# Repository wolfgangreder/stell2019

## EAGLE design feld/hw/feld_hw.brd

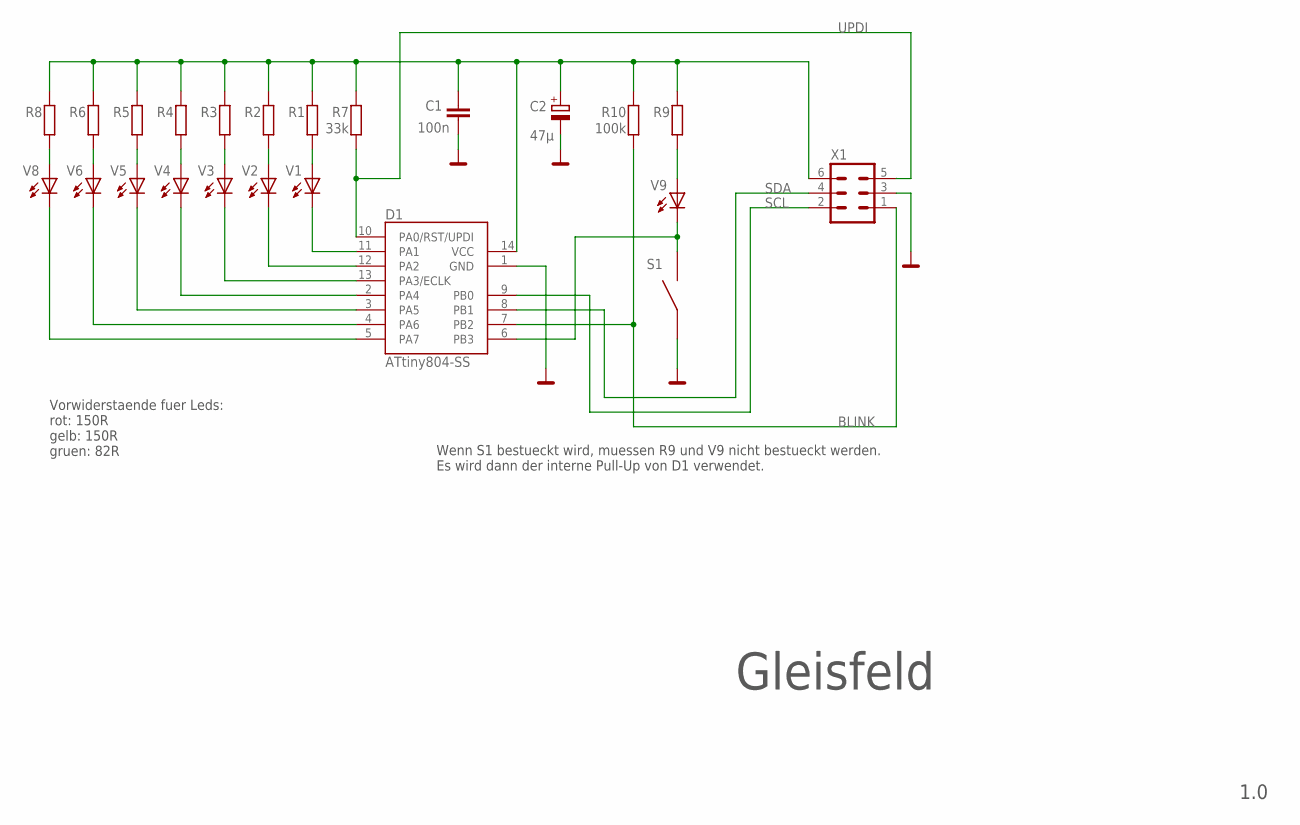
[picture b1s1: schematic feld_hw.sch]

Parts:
C1: 100n; C0805
C2: 47µ; CT7343
D1: ATtiny804-SS; SOIC14
R1, R2, R3, R4, R5, R6, R8, R9: R-EU_R0805; R0805
R7: 33k; R0805
R10: 100k; R0805
S1: 800SP9B5M2QEH; ST811004
V1, V2, V3, V4, V5, V6, V8, V9: LEDPAD; LED3MMPAD
X1: PINH2X3N; MA03/2

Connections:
BLINK: D1.7 (PB2), R10.1, X1.1
GND: C1.1, C2.-, D1.1 (GND), S1.1, X1.3
unnamed: D1.5 (PA7), V8.P$2 (C)
unnamed: D1.4 (PA6), V6.P$2 (C)
unnamed: D1.3 (PA5), V5.P$2 (C)
unnamed: D1.2 (PA4), V4.P$2 (C)
unnamed: D1.13 (PA3/ECLK), V3.P$2 (C)
unnamed: D1.12 (PA2), V2.P$2 (C)
unnamed: D1.11 (PA1), V1.P$2 (C)
unnamed: R8.1, V8.P$1 (A)
unnamed: R6.1, V6.P$1 (A)
unnamed: R5.1, V5.P$1 (A)
unnamed: R4.1, V4.P$1 (A)
unnamed: R3.1, V3.P$1 (A)
unnamed: R2.1, V2.P$1 (A)
unnamed: R1.1, V1.P$1 (A)
unnamed: C1.2, C2.+, D1.14 (VCC), R1.2, R2.2, R3.2, R4.2, R5.2, R6.2, R7.2, R8.2, R9.2, R10.2, X1.6
unnamed: D1.6 (PB3), S1.2, V9.P$2 (C)
unnamed: R9.1, V9.P$1 (A)
SCL: D1.9 (PB0), X1.2
SDA: D1.8 (PB1), X1.4
UPDI: D1.10 (PA0/RST/UPDI), R7.1, X1.5

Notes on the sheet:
Vorwiderstaende fuer Leds: rot: 150R gelb: 150R gruen: 82R
Wenn S1 bestueckt wird, muessen R9 und V9 nicht bestueckt werden. Es wird dann der interne Pull-Up von D1 verwendet.
Gleisfeld
1.0

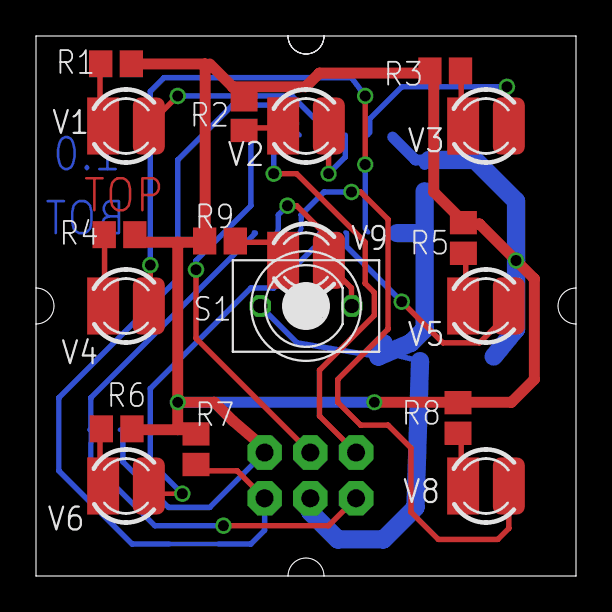
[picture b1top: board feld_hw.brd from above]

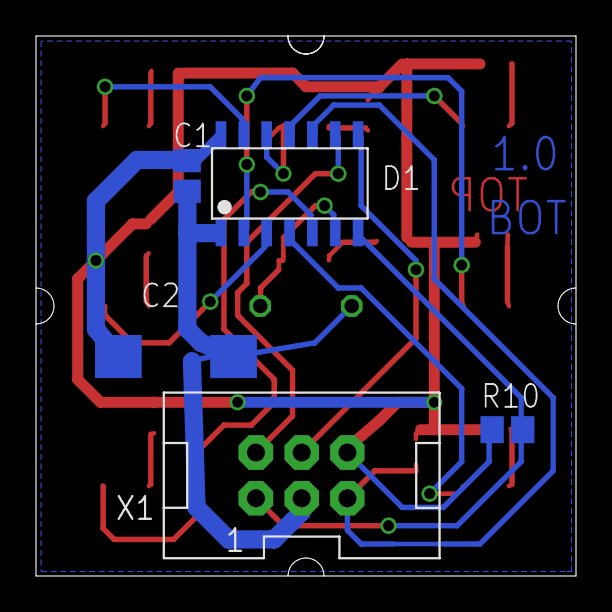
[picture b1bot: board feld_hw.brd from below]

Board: 2 copper layers, 30.0 x 30.0 mm, 23 parts (5 on the bottom side), 22 nets.

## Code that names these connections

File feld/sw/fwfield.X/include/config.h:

/*
 * File:   hw.h
 * Author: wolfi
 *
 * Created on 28. November 2019, 18:01
 */

#ifndef HW_H
#define	HW_H
#include <avr/io.h>
#include <avr/eeprom.h>
#include <avr/pgmspace.h>
#include <avr/interrupt.h>
#include "types.h"

#ifdef	__cplusplus
extern "C" {
#endif



#ifndef TWI_ADDRESS
#define TWI_ADDRESS 3
#endif

#ifndef FW_MAJOR
#define FW_MAJOR 0
#endif

#ifndef FW_MINOR
#define FW_MINOR 0
#endif


#ifndef IND_DEBUG
#define IND_DEBUG 0
#endif

#if IND_DEBUG==1
#define IND_PORT PORTA
#define IND_DIR DDRA
#define IND_0_OFF (IND_PORT&=~_BV(PA0))
#define IND_0_ON (IND_PORT|=_BV(PA0))
#define IND_1_OFF (IND_PORT&=~_BV(PA1))
#define IND_1_ON (IND_PORT|=_BV(PA1))
#define IND_2_OFF (IND_PORT&=~_BV(PA2))
#define IND_2_ON (IND_PORT|=_BV(PA2))
#define IND_3_OFF (IND_PORT&=~_BV(PA3))
#define IND_3_ON (IND_PORT|=_BV(PA3))
#define IND_INIT   IND_DIR |= (_BV(PA0)|_BV(PA1)|_BV(PA2)|_BV(PA3));
#elif IND_DEBUG==2
#undef IND_0_OFF
#undef IND_0_ON
#undef IND_1_OFF
#undef IND_1_ON
#undef IND_2_OFF
#undef IND_2_ON
#undef IND_3_OFF
#undef IND_3_ON
#undef IND_INIT
#else
#define IND_0_OFF
#define IND_0_ON
#define IND_1_OFF
#define IND_1_ON
#define IND_2_OFF
#define IND_2_ON
#define IND_3_OFF
#define IND_3_ON
#define IND_INIT
#endif

#define TIMER1_PRESCALE_MASK (_BV(CS10)|_BV(CS11)|_BV(CS12))
#define TIMER1_PRESCALE_1 _BV(CS10)
#define TIMER1_PRESCALE_8 _BV(CS11)
#define TIMER1_PRESCALE_64 (_BV(CS10)|_BV(CS11))
#define TIMER1_PRESCALE_256 _BV(CS12)
#define TIMER1_PRESCALE_1024 (_BV(CS12)|_BV(CS10))

#ifdef _AVR_IOM8535_H_
#define FREQ 14745600
#define DEVICE 8535
#define PORT_LED PORTB
#define DDR_LED DDRB
#define PIN_LED PINB
#define LED_1 0
#define LED_2 1
#define LED_3 2
#define LED_4 3
#define LED_5 4
#define LED_6 5
#define LED_8 6
#define LED_9 7
#define SWITCH_PORT PORTD
#define SWITCH_DIR DDRD
#define SWITCH_PIN PIND
#define SWITCH 2
#define SWITCH_INT_vect INT0_vect
#define SWITCH_INT_ENABLE _BV(INT0)
#define SWITCH_MCU_OR _BV(ISC00)
#define SWITCH_MCU_AND (~_BV(ISC01))
#define PORT_BLINK PORTD
#define DDR_BLINK DDRD
#define PIN_BLINK PIND
#define BLINK 3
#define BLINK_INT_vect INT1_vect
#define BLINK_MCU_OR _BV(ISC11)
#define BLINK_MCU_AND (~_BV(ISC10))
#define BLINK_INT_ENABLE _BV(INT1)
#define MS_TIMER_PRESCALE TIMER1_PRESCALE_64
#define MS_TIMER_OCR 231
#define BLINK_PRESCALE_INIT 62
#define BAUD_TWI 66 // 100k
#define PRESC_TWI 0
#define PORT_TWI PORTC
#define DDR_TWI DDRC
#define PIN_TWI PINC
#define SDA PC1
#define SCL PC0
#else
#error device not supported
#endif

  typedef enum {
    REG_STATE = 0,
    REG_LED = 1,
    REG_BLINKMASK = 2,
    REG_BLINKPHASE = 3,
    REG_PWM = 4,
    REG_MODULESTATE = 5,
    REG_VCC = 6,
    REG_BLINKDIVIDER = 7,
    REG_ADDRESS_MSB = 8,
    REG_ADDRESS_LSB = 9,
    REG_MODULETYPE = 10,
    REG_DEBOUNCE = 11,
    REG_VCC_CALIBRATION = 12,
    REG_DEFAULT_PWM = 13,
    REG_VERSION = 14,
    REG_VCC_REFERENCE = 15
  } register_t;

  typedef struct {

    union {
      uint16_t address;

      struct {
        uint8_t address_msb;
        uint8_t address_lsb;
      };
    };
    uint8_t moduletype;
    uint8_t debounce;
    uint8_t softstart;
    uint8_t softstop;
    int8_t vcc_calibration;
    uint8_t defaultPWM;
    uint8_t twibaud;
    uint8_t twipresc;
    uint16_t masterAddress;

  } TEEPromFile;

  typedef struct {

    union {
      uint8_t state;

      struct {
        bool key_pressed : 1; // 1 wenn taste gedrückt
        uint8_t reserved : 5;
        bool bo_error : 1; // 1 wenn brown out reset
        bool wdt_error : 1; // 1 wenn watchdog reset
      };
    };
    uint8_t led; // 1-> led an
    uint8_t blinkmask; // 1-> led blinkt
    uint8_t blinkphase; // 1-> led blinkt invers
    uint8_t pwm; // helligkeit
    uint8_t modulstate; // weiche gerade/ablenkung etc
    uint16_t vcc; // vcc mV;
    uint8_t blinkdivider;

  } TRegisterFile;

  typedef struct {

    union {
      uint16_t fw_Version;

      struct {
        uint8_t fw_major;
        uint8_t fw_minor;
      };
    };
  } TFlashFile;

  typedef enum {
    OP_READ = 0,
    OP_WRITE = 1,
    OP_INCREMENT = 2,
    OP_DECREMENT = 3,
    OP_COMPLEMENT = 4
  } operation_t;

  typedef union {
    uint8_t raw[4];

    struct {
      uint8_t rxSlaveAddress;
      uint8_t rxRegisterAddress;
      operation_t rxRegisterOperation;
      uint8_t rxData;
    };

    struct {
      uint8_t txSlaveAddress;
      uint8_t txOwnAddress;

      union {
        uint16_t txWData;

        struct {
          uint8_t txA;
          uint8_t txB;
        };
      };
    };

  } TDataPacket;

  extern TRegisterFile registerFile;
  extern EEMEM TEEPromFile ee_eepromFile;
  extern TEEPromFile eepromFile;
  extern const PROGMEM TFlashFile fl_flashFile;
  extern TFlashFile flashFile;

  inline void enableSwitch() {
    MCUCR |= SWITCH_MCU_OR;
    MCUCR &= SWITCH_MCU_AND;
    GICR |= SWITCH_INT_ENABLE;
    SWITCH_DIR &= ~_BV(SWITCH);
    SWITCH_PORT |= _BV(SWITCH);
  }

  inline void disableSwitch() {
    GICR &= ~SWITCH_INT_ENABLE;
  }


  extern void initHW();
  extern uint16_t processState();
  extern uint16_t processLed(uint8_t led, operation_t operation);
  extern uint16_t processBlinkMask(uint8_t led, operation_t operation);
  extern uint16_t processBlinkPhase(uint8_t lef, operation_t operation);
  extern uint16_t processBlinkDivider(uint8_t val, operation_t operation);
  extern uint16_t processPWM(uint8_t pwm, operation_t operation);
  extern uint16_t processDefaultPWM(uint8_t pwm, operation_t operation);
  extern uint16_t processVCC();
  extern uint16_t processVCCCalibration(uint8_t cal, operation_t operation);
  extern uint16_t processDebounce(uint8_t val, operation_t operation);
  extern uint16_t processFirmwareVersion();
  extern uint16_t processModuleType(uint8_t moduleType, operation_t operation);

#define TWI_ADDR 3
#define TWI_BAUD 66

#ifdef	__cplusplus
}
#endif

#endif	/* HW_H */

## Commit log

2019-08-12 Release 2019-08-12
2019-11-18 Schalten Funkt. GetAccessoryState liefert invertiertes? ergebnis (01:04:Request) CV Programmieren funkt nur beim ersten mal, danach state 0x80 (busy) Mcastport implementiert, hat aber noch viele fehl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
2019-11-25 Closeverhalten bezüglich Exceptions verbessert.
2020-01-19 fwfield für m8535 fertig (Version 0.10)
2020-01-19 fwfield für m8535 fertig (Version 0.14)
2020-11-23 +EDK750
2020-11-23 EDK750 + emergencyMode + isStarted
2020-11-23 CommandGroup CONFIG(0x18) soweit bekannt implementiert (Tachoevents)
2020-11-25 EDK750 kann dynamisch mit Locomotive verbunden und getrennt werden. Notwendig wenn ein Verbindungsabriss war.
2020-11-27 fixed bug: f11 war keine togglefunktion
2020-11-28 Geschwindigkeitsregelung Kranfunktionen EDK750 implementiert.
